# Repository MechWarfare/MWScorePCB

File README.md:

# MWScorePCB
EagleCAD files for all 3 PCBs used in MWScore setup

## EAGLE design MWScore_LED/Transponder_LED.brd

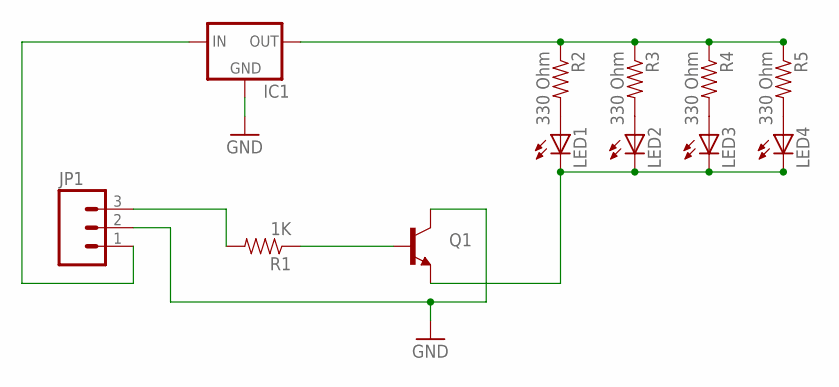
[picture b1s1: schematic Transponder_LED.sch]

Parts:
IC1: V_REG_78XXTO-92; TO-92
JP1: M03JST-PTH; JST-3-PTH
LED1, LED2, LED3, LED4: LED5MM
Q1: TRANSISTOR_NPNTO92; TO-92
R1: 1K; AXIAL-0.4
R2, R3, R4, R5: 330 Ohm; AXIAL-0.4

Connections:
GND: IC1.1 (GND), JP1.2, Q1.3 (C)
unnamed: IC1.2 (IN), JP1.1
unnamed: Q1.2 (B), R1.P$1 (1)
unnamed: JP1.3, R1.P$2 (2)
unnamed: LED1.A, R2.P$2 (2)
unnamed: LED2.A, R3.P$2 (2)
unnamed: LED3.A, R4.P$2 (2)
unnamed: LED4.A, R5.P$2 (2)
unnamed: IC1.3 (OUT), R2.P$1 (1), R3.P$1 (1), R4.P$1 (1), R5.P$1 (1)
unnamed: LED1.K (C), LED2.K (C), LED3.K (C), LED4.K (C), Q1.1 (E)

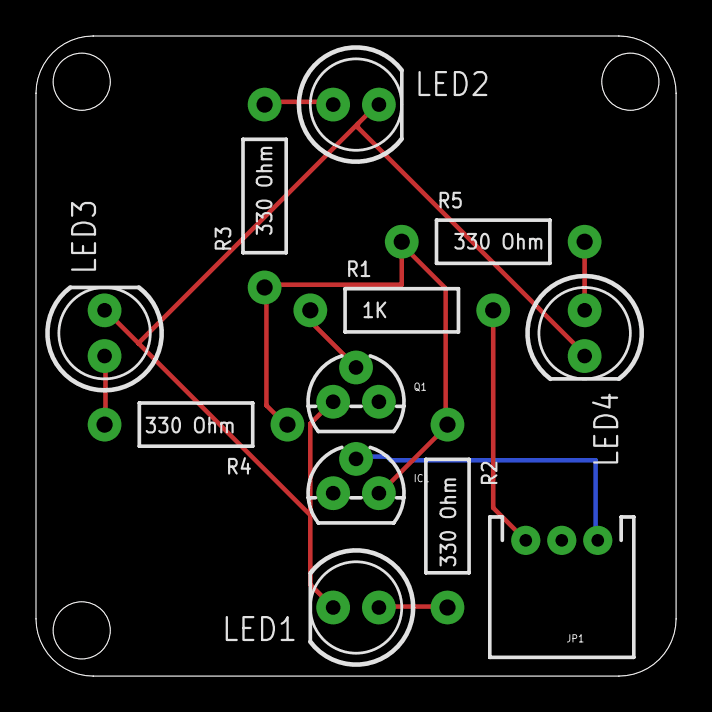
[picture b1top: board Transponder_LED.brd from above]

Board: 2 copper layers, 35.6 x 35.6 mm, 12 parts (0 on the bottom side), 10 nets.

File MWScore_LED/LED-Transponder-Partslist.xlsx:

Item No. | QTY | Ref. | Description | Part Number | Package
1 | 1 | Q1 | 2N2222 | P2N2222AGOS-ND | TO-92
2 | 1 | IC1 | 5v LDO VREG | MCP1702-5002E/TO-ND | TO-92
3 | 4 | LED1,2,3,4 | Red, Ultra-brite LED | 1080-1133-ND
4 | 1 | JP1 | CONN Header PH Side 3POS 2MM JST | 455-1720-ND | JST
5 | 1 | R1 | 1/4w 0.4" 1k Ohm Resistor | CF14JT1K00CT-ND
6 | 4 | R2,3,4,5 | 1/4w 0.4" 330 Ohm Resistor | CF14JT330RCT-ND

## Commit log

2015-02-02 First push

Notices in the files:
parts and their libraries:
SparkFun: Licensing: CC v3.0 Share-Alike You are welcome to use this library for commercial purposes.
